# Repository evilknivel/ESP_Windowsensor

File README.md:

# ESP_Windowsensor
door sensor with attiny and esp

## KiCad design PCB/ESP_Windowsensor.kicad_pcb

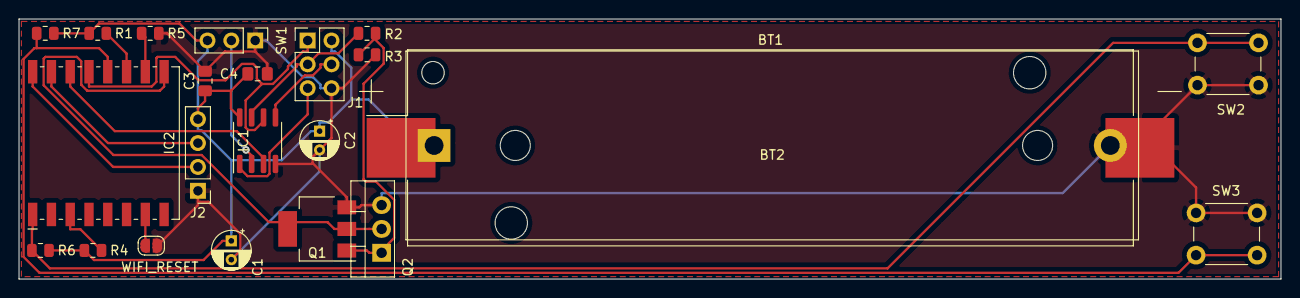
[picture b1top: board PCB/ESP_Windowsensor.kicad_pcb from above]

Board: 2 copper layers, 134.4 x 27.7 mm, 23 parts (0 on the bottom side), 18 nets.

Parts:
BT1: Battery_Cell; BatteryHolder_Keystone_1042_1x18650
BT2: Battery_Cell; BatteryHolder_MPD_BH-18650-PC2
C1, C2: 4,7µ; CP_Radial_D4.0mm_P2.00mm
C3, C4: 100n; C_0805_2012Metric_Pad1.18x1.45mm_HandSolder
IC1: ATtiny13A-SSU; SOIC-8_3.9x4.9mm_P1.27mm
IC2: ESP-07
J1: AVR-ISP-6; PinHeader_2x03_P2.54mm_Vertical
J2: Conn_01x04_Female; PinHeader_1x04_P2.54mm_Vertical
Q1: IRLML6244; SOT-223-3_TabPin2
Q2: IRF3708; TO-220-3_Vertical
R1, R3, R4, R5, R6, R7: 10k; R_0805_2012Metric
R2: 100; R_0805_2012Metric
SW1: SW_Reed_SPDT; PinHeader_1x03_P2.54mm_Vertical
SW2, SW3: SW_Push; SW_PUSH_6mm
WIFI_RESET: SolderJumper_2_Open; SolderJumper-2_P1.3mm_Open_RoundedPad1.0x1.5mm

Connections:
+BATT: BT1.1, BT2.1, C1.1, C2.1, C3.1, C4.1, IC1.8, J1.2, J2.4, R1.1, R4.1, R6.1, R7.1, SW1.3
ESP_BOOT: IC2.12, R7.2, SW3.1
ESP_ON: Q1.1, Q2.1, R2.2, R3.1
ESP_READY: IC1.3, IC2.14
ESP_RST: IC2.1, R6.2, SW2.1
GND: BT1.2, BT2.2, C1.2, C2.2, C3.2, C4.2, IC1.4, J1.6, J2.1, Q1.3, Q2.3, R3.2, R5.2, SW1.1, SW2.2, SW3.2, WIFI_RESET.1
ISP_MISO: IC1.6, IC2.13, J1.1
ISP_MOSI: IC1.5, J1.4
ISP_RST: IC1.1, J1.5
ISP_SCK: IC1.7, J1.3, R2.1
unnamed: IC2.3, R4.2
unnamed: IC2.7, WIFI_RESET.2
unnamed: IC2.9, Q1.2, Q2.2
unnamed: IC2.10, R5.1
unnamed: IC2.11, R1.2
RX: IC2.15, J2.3
SENSOR: IC1.2, SW1.2
TX: IC2.16, J2.2

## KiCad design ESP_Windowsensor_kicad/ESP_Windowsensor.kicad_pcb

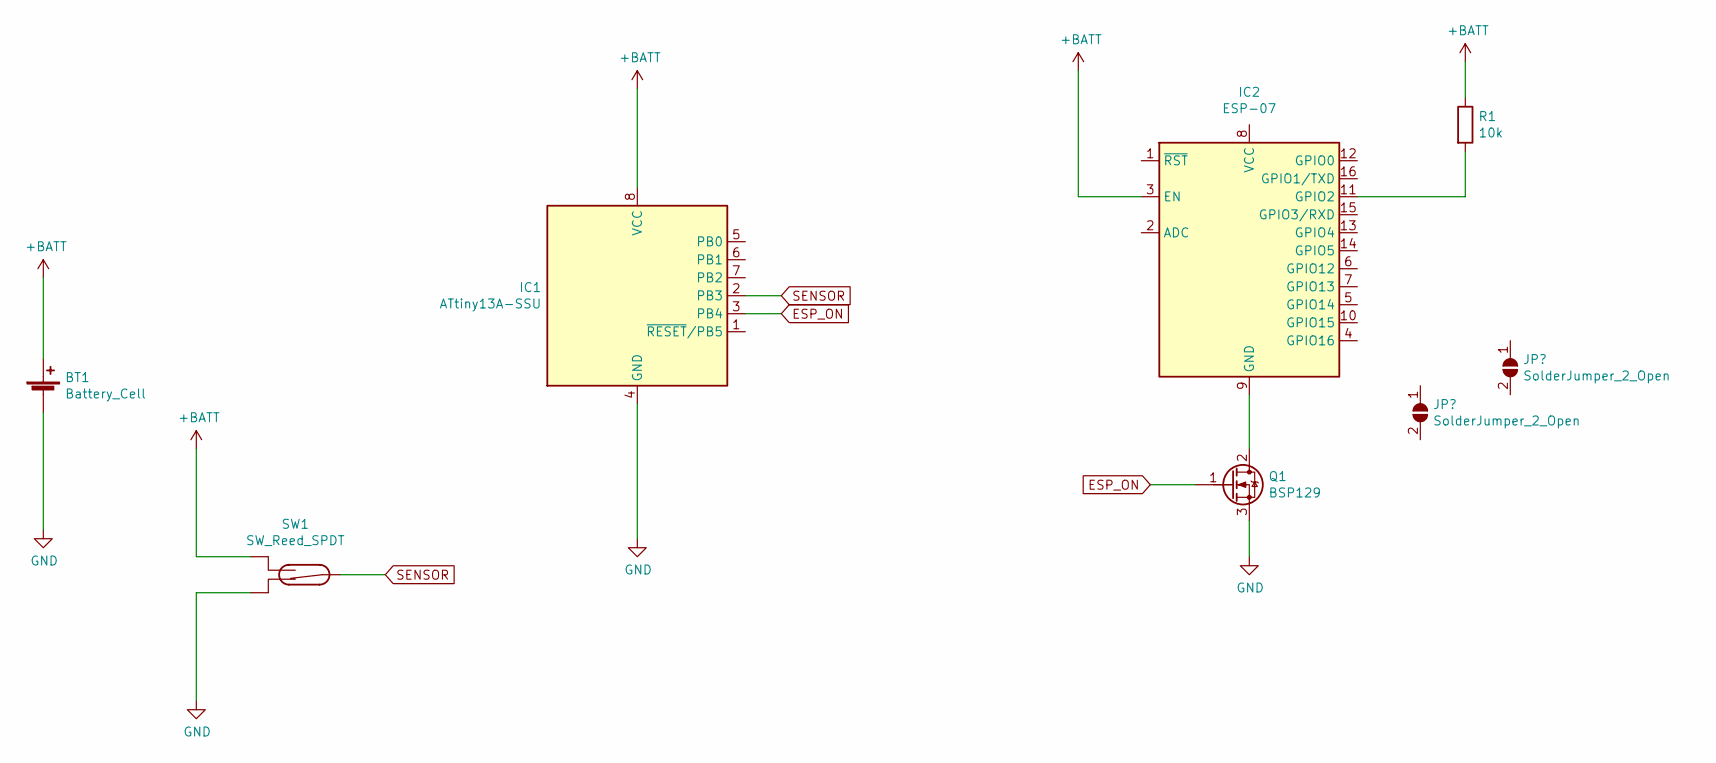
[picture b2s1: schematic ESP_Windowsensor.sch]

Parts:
BT1: Battery_Cell; BatteryHolder_Keystone_1042_1x18650
IC1: ATtiny13A-SSU; SOIC-8_3.9x4.9mm_P1.27mm
IC2: ESP-07
Q1: BSP129; SOT-223-3_TabPin2
R1: 10k; R_0805_2012Metric
SW1: SW_Reed_SPDT; PinHeader_1x03_P2.54mm_Vertical

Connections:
+BATT: BT1.1 (+), IC1.8 (VCC), IC2.3 (EN), R1.1, SW1.3
ESP_ON: IC1.3 (PB4), Q1.1 (G)
GND: BT1.2 (-), IC1.4 (GND), Q1.3 (S), SW1.1
unnamed: IC2.9 (GND), Q1.2 (D)
unnamed: IC2.11 (GPIO2), R1.2
SENSOR: IC1.2 (PB3), SW1.2

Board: 2 copper layers, 6 parts (0 on the bottom side), 6 nets, no tracks yet.

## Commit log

2021-03-21 GITIGNORE und GITATTRIBUTES hinzufügen.
2021-03-23 init
2021-03-26 Create firmware.ino
    init
2021-03-29 Create READ.ME
    init
2021-03-29 Add files via upload
    init
2021-03-29 Add files via upload
    upload board rev 0.1
